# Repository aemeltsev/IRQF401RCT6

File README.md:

License
-------

IRQF401RCT6 schematic files and documentations are distributed under 
Creative Commons Attribution 4.0 International License.

Overview
--------
Simply dev. board based STM32F401RCT6. And includes in self: i2c eeprom memory and RS485 transceiver ic.

![PCB image][pcb_ray]

[pcb_ray]: https://github.com/aemeltsev/IRQF401RCT6/blob/master/doc/pcb_ray.png

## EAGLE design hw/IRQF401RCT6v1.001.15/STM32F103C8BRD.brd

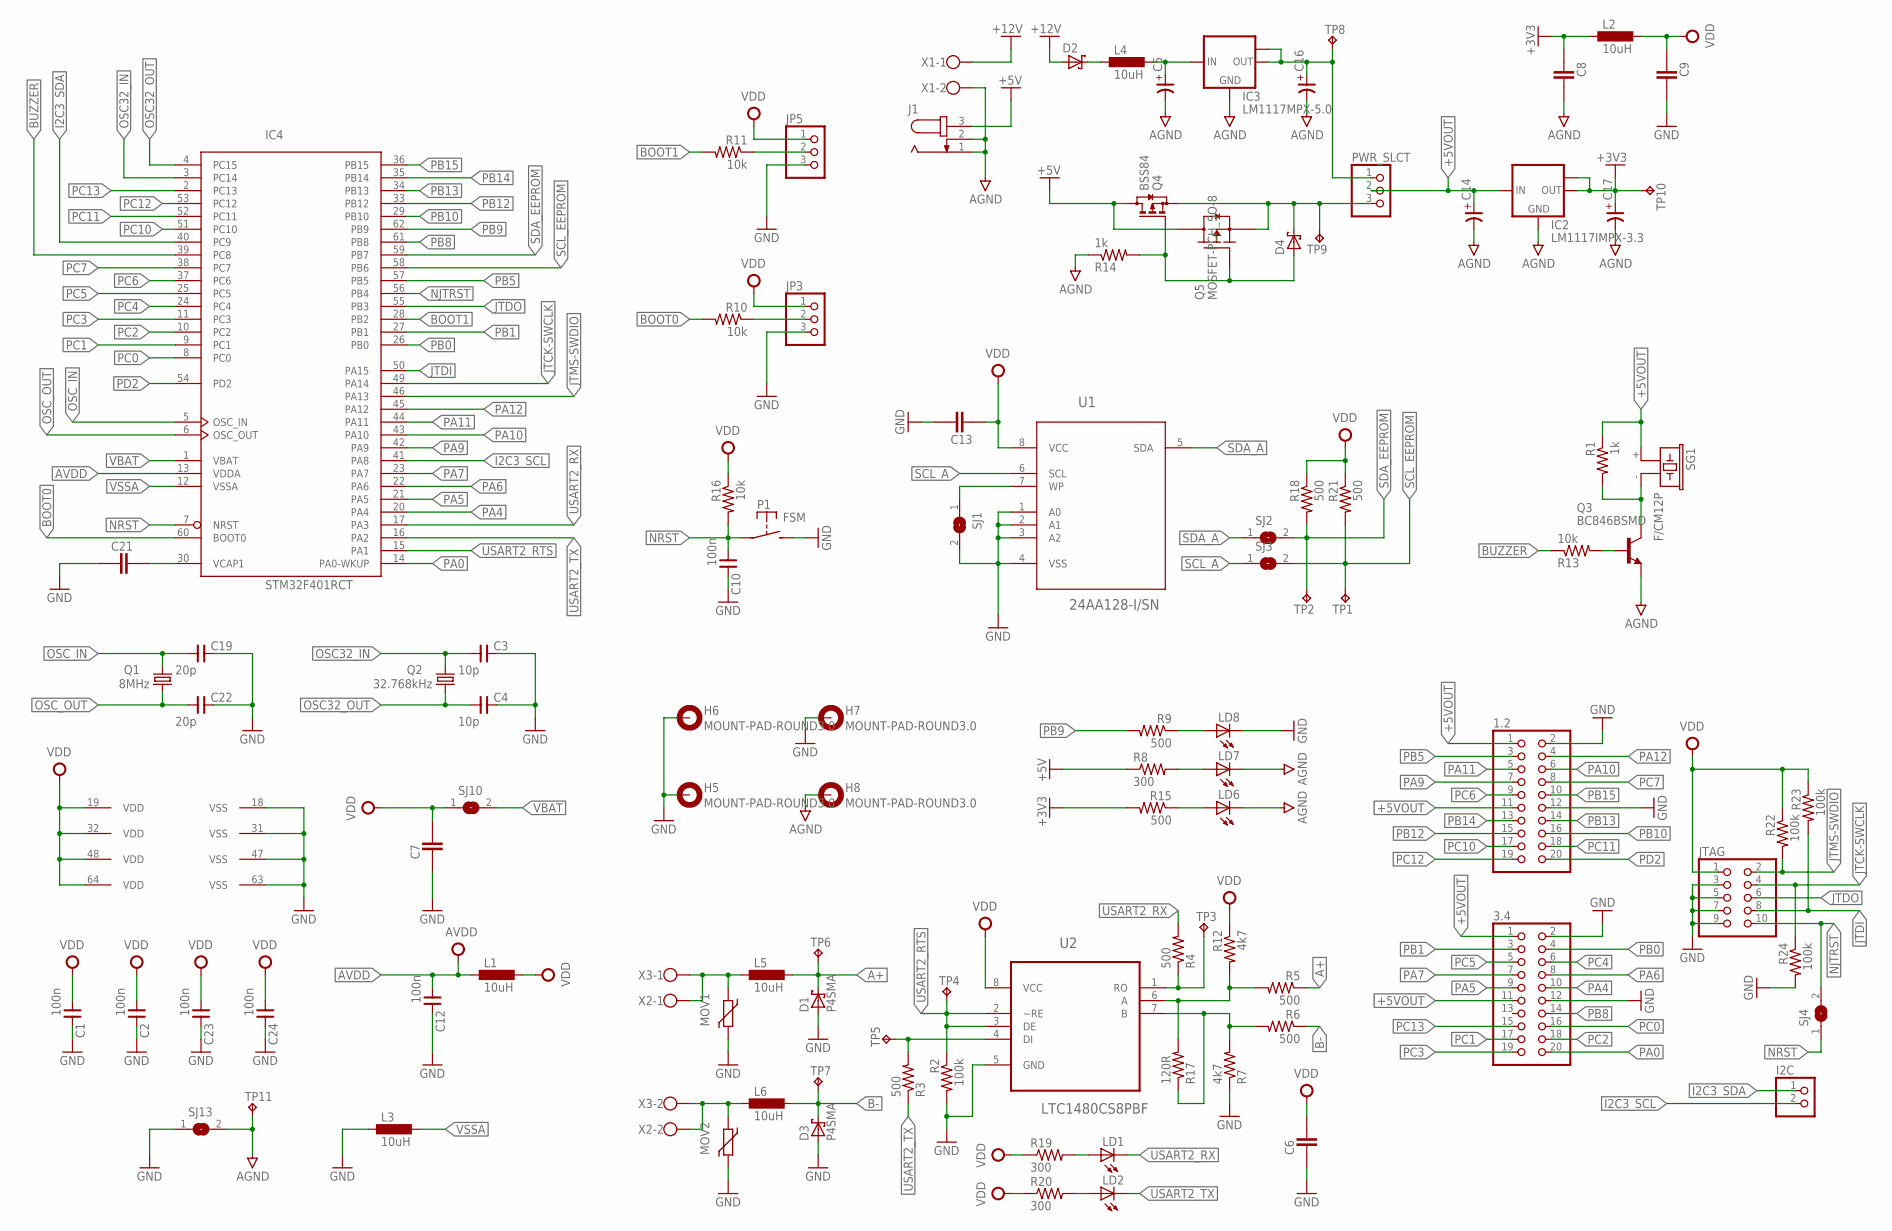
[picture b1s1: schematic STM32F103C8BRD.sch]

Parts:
1.2, 3.4: PINHD-2X10; 2X10
C1, C2, C10, C12, C23, C24: 100n; 0805
C3, C4: 10p; 0805
C5, C14: CP-3258-TE-B; 3528-TE-B
C6, C7, C8, C9, C13, C21: CAPACITOR_1206; CAPC3215X168N
C16, C17: CP-3216-TE-A; 3216-TE-A
C19, C22: 20p; 0805
D1, D3: P4SMA; SMB
D2, D4: SCHOTTKY_SMA; DIOM5326X292N
H5, H6, H7, H8: MOUNT-PAD-ROUND3.0; 3,0-PAD
I2C: PINHD-1X2; 1X02
IC2: LM1117IMPX-3.3; SOT223
IC3: LM1117MPX-5.0; SOT223
IC4: STM32F401RCT; LQFP64
J1: JACK-PLUG1; SPC4078
JP3, JP5: PINHD-1X3; 1X03
JTAG: PINHD-2X5; 2X05
L1, L2, L3, L4, L5, L6: 10uH; INDC1608X95N
LD1, LD2, LD6, LD7, LD8: LEDCHIPLED_0805; CHIPLED_0805
MOV1, MOV2: VARISTOR_0805; VARC2012X70N
P1: FSM
PWR_SLCT: PINHD-1X3; 1X03
Q1: 8MHz; HC49/S
Q2: 32.768kHz; TC26H
Q3: BC846BSMD; SOT23
Q4: BSS84; SOT23
Q5: MOSFET-PCH_SO-8; SOIC127P600X175-8AN
R1, R14: 1k; M0805
R2, R22, R23, R24: 100k; M0805
R3, R4, R5, R6, R9, R15, R18, R21: 500; M0805
R7, R12: 4k7; M0805
R8, R19, R20: 300; M0805
R10, R11, R13, R16: 10k; M0805
R17: 120R; M0805
SG1: F/CM12P
SJ1, SJ2, SJ3, SJ4, SJ10, SJ13: SJ
TP1, TP2, TP3, TP4, TP5, TP6, TP7, TP8, TP9, TP10, TP11: TPTP10R; TP10R
U1: 24AA128-I/SN; SOIC127P600X175-8N
U2: LTC1480CS8PBF; SOIC127P600X175-8N
X1, X2, X3: W237-102

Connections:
+3V3: C8.1, C17.+, IC2.2 (OUT), IC2.TAB (OUT1), L2.1, R15.2, TP10.TP
+5V: J1.3, Q4.3 (D), Q5.5 (D), R8.1
+5VOUT: 1.2.1, 1.2.11, 3.4.1, 3.4.11, C14.+, IC2.3 (IN), PWR_SLCT.2, R1.1, SG1.+ (1)
+12V: D2.A, X1.1
A+: D1.C, L5.2, R5.1, TP6.TP
AGND: C5.-, C8.2, C14.-, C16.-, C17.-, H8.B3,0, IC2.1 (GND), IC3.1 (GND), J1.1, J1.2, LD6.C, LD7.C, Q3.2 (E), R14.1, SJ13.2, TP11.TP, X1.2
AVDD: C12.1, IC4.13 (VDDA), L1.1
B-: D3.C, L6.2, R6.1, TP7.TP
BOOT0: IC4.60 (BOOT0), R10.2
BOOT1: IC4.28 (PB2), R11.2
BUZZER: IC4.39 (PC8), R13.1
GND: 1.2.2, 1.2.12, 3.4.2, 3.4.12, C1.2, C2.2, C3.2, C4.2, C6.1, C7.1, C9.2, C10.2, C12.2, C13.2, C19.2, C21.1, C22.2, C23.2, C24.2, D1.A, D3.A, H5.B3,0, H6.B3,0, H7.B3,0, IC4.18 (VSS), IC4.31 (VSS), IC4.47 (VSS), IC4.63 (VSS), JP3.3, JP5.3, JTAG.3, JTAG.5, JTAG.7, JTAG.9, L3.1, LD8.C, MOV1.1, MOV2.1, P1.P$2 (S), R2.2, R7.1, R24.2, SJ1.2, SJ13.1, U1.1 (A0), U1.2 (A1), U1.3 (A2), U1.4 (VSS), U2.5 (GND)
I2C3_SCL: I2C.2, IC4.41 (PA8)
I2C3_SDA: I2C.1, IC4.40 (PC9)
JTCK-SWCLK: IC4.49 (PA14), JTAG.4, R24.1
JTDI: IC4.50 (PA15), JTAG.8, R23.2
JTDO: IC4.55 (PB3), JTAG.6
JTMS-SWDIO: IC4.46 (PA13), JTAG.2, R22.2
unnamed: SJ1.1, U1.7 (WP)
unnamed: C21.2, IC4.30 (VCAP1)
unnamed: D2.K, L4.1
unnamed: R6.2, R7.2, R17.1, U2.7 (B)
unnamed: JP3.2, R10.1
unnamed: LD7.A, R8.2
unnamed: R3.2, TP5.TP, U2.4 (DI)
unnamed: R5.2, R12.2, R17.2, U2.6 (A)
unnamed: C5.+, IC3.3 (IN), L4.2
unnamed: L5.1, MOV1.2, X2.1, X3.1
unnamed: L6.1, MOV2.2, X2.2, X3.2
unnamed: R4.1, TP3.TP, U2.1 (RO)
unnamed: LD8.A, R9.1
unnamed: Q3.3 (C), R1.2, SG1.- (2)
unnamed: Q3.1 (B), R13.2
unnamed: LD6.A, R15.1
unnamed: LD1.A, R19.2
unnamed: LD2.A, R20.2
unnamed: D4.A, Q4.1 (G), Q5.4 (G), R14.2
unnamed: D4.K, PWR_SLCT.3, Q4.2 (S), Q5.1 (S), TP9.TP
NJTRST: IC4.56 (PB4), JTAG.10, SJ4.2
NRST: C10.1, IC4.7 (NRST), P1.P$1, R16.2, SJ4.1
OSC32_IN: C3.1, IC4.3 (PC14), Q2.2
OSC32_OUT: C4.1, IC4.4 (PC15), Q2.1
OSC_IN: C19.1, IC4.5 (OSC_IN), Q1.2
OSC_OUT: C22.1, IC4.6 (OSC_OUT), Q1.1
PA0: 3.4.20, IC4.14 (PA0-WKUP)
PA4: 3.4.10, IC4.20 (PA4)
PA5: 3.4.9, IC4.21 (PA5)
PA6: 3.4.8, IC4.22 (PA6)
PA7: 3.4.7, IC4.23 (PA7)
PA9: 1.2.7, IC4.42 (PA9)
PA10: 1.2.6, IC4.43 (PA10)
PA11: 1.2.5, IC4.44 (PA11)
PA12: 1.2.4, IC4.45 (PA12)
PB0: 3.4.4, IC4.26 (PB0)
PB1: 3.4.3, IC4.27 (PB1)
PB2: JP5.2, R11.1
PB5: 1.2.3, IC4.57 (PB5)
PB8: 3.4.14, IC4.61 (PB8)
PB9: IC4.62 (PB9), R9.2
PB10: 1.2.16, IC4.29 (PB10)
PB12: 1.2.15, IC4.33 (PB12)
PB13: 1.2.14, IC4.34 (PB13)
PB14: 1.2.13, IC4.35 (PB14)
PB15: 1.2.10, IC4.36 (PB15)
PC0: 3.4.16, IC4.8 (PC0)
PC1: 3.4.17, IC4.9 (PC1)
PC2: 3.4.18, IC4.10 (PC2)
PC3: 3.4.19, IC4.11 (PC3)
PC4: 3.4.6, IC4.24 (PC4)
PC5: 3.4.5, IC4.25 (PC5)
PC6: 1.2.9, IC4.37 (PC6)
PC7: 1.2.8, IC4.38 (PC7)
PC10: 1.2.17, IC4.51 (PC10)
PC11: 1.2.18, IC4.52 (PC11)
PC12: 1.2.19, IC4.53 (PC12)
PC13: 3.4.15, IC4.2 (PC13)
PD2: 1.2.20, IC4.54 (PD2)
SCL_A: SJ3.1, U1.6 (SCL)
SCL_EEPROM: IC4.58 (PB6), R21.2, SJ3.2, TP1.TP
SDA_A: SJ2.1, U1.5 (SDA)
SDA_EEPROM: IC4.59 (PB7), R18.2, SJ2.2, TP2.TP
USART2_RTS: IC4.15 (PA1), R2.1, TP4.TP, U2.2 (~RE), U2.3 (DE)
USART2_RX: IC4.17 (PA3), LD1.C, R4.2
USART2_TX: IC4.16 (PA2), LD2.C, R3.1
VBAT: IC4.1 (VBAT), SJ10.2
VCC_OUT: C16.+, IC3.2 (OUT), IC3.TAB (OUT1), PWR_SLCT.1, TP8.TP
VDD: C1.1, C2.1, C6.2, C7.2, C9.1, C13.1, C23.1, C24.1, IC4.19 (VDD), IC4.32 (VDD), IC4.48 (VDD), IC4.64 (VDD), JP3.1, JP5.1, JTAG.1, L1.2, L2.2, R12.1, R16.1, R18.1, R19.1, R20.1, R21.1, R22.1, R23.1, SJ10.1, U1.8 (VCC), U2.8 (VCC)
VSSA: IC4.12 (VSSA), L3.2

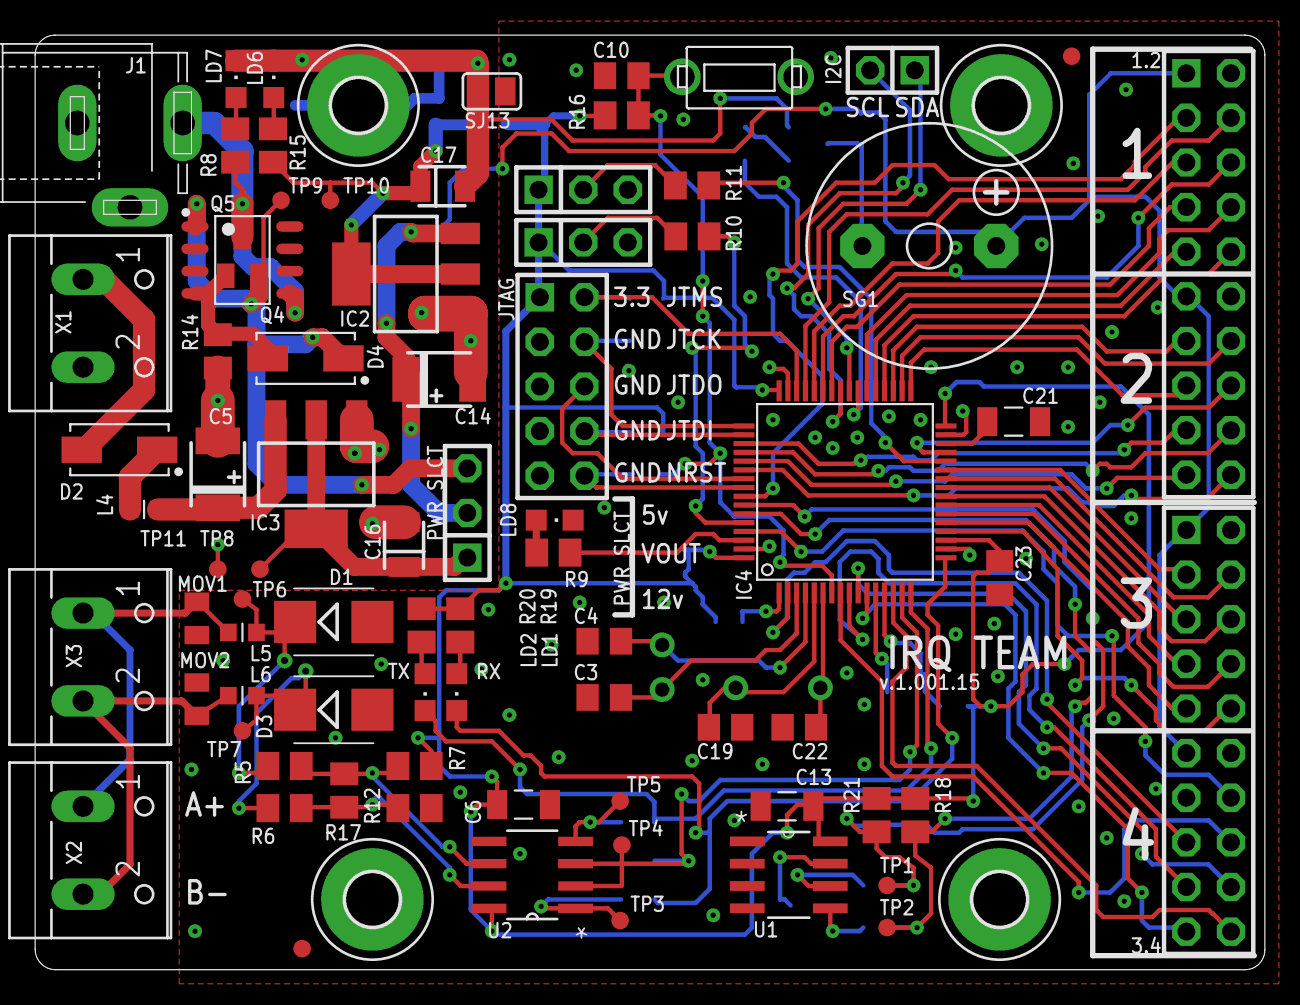
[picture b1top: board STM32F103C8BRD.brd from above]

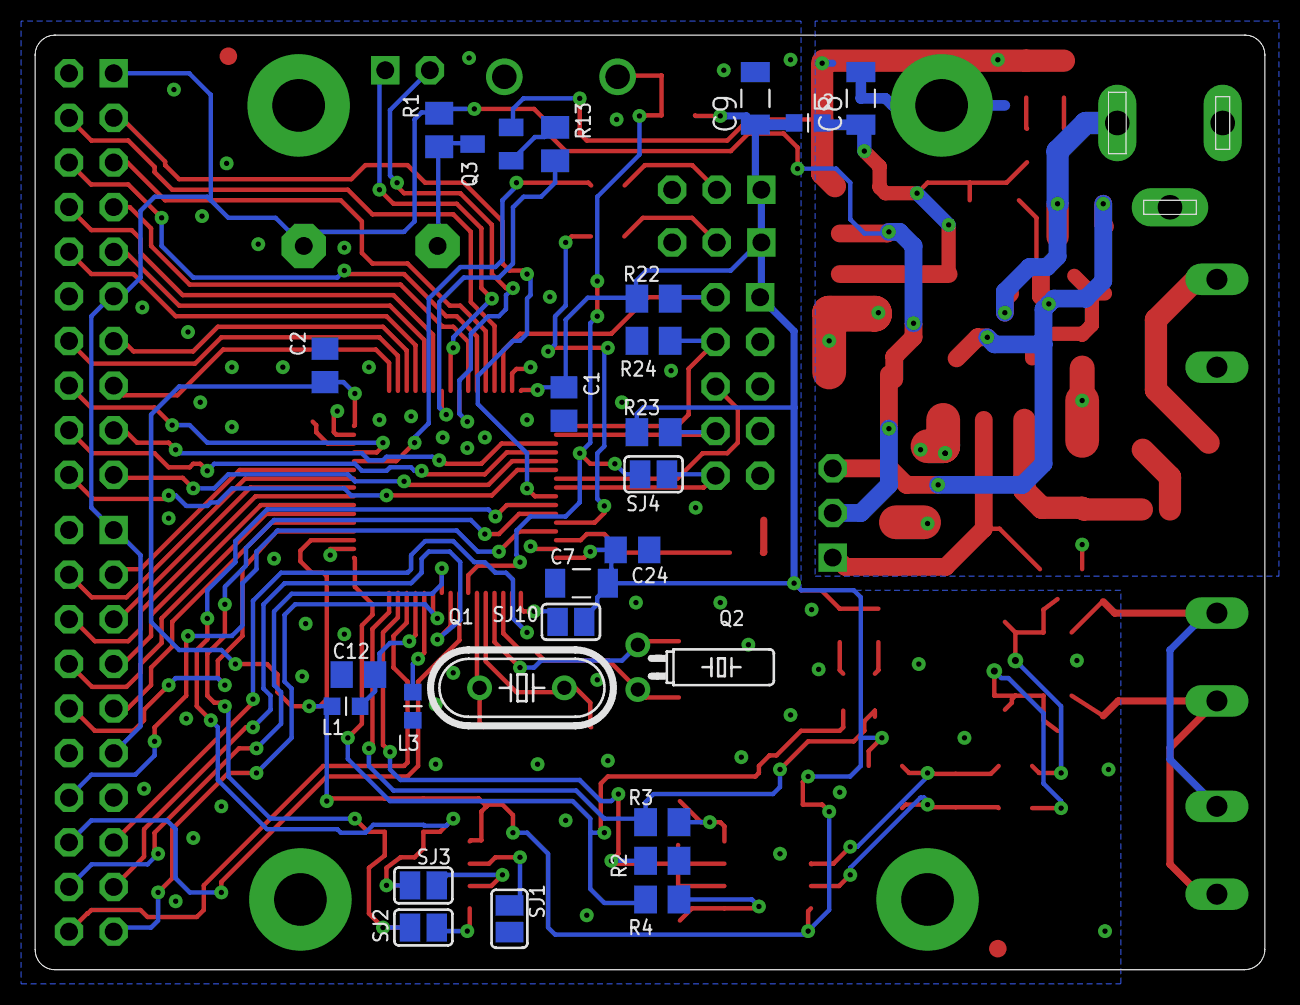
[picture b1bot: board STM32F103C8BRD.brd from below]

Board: 2 copper layers, 70.0 x 53.2 mm, 107 parts (26 on the bottom side), 88 nets.

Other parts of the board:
U$3, U$4: FIDUCIAL_G10

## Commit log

2017-10-18 :tada: Added .gitattributes & .gitignore files
2017-10-18 Add fifes
    Add schematic & doc files
2019-01-13 Create README.md
    add Readme
2019-01-13 Add files
    Add project files, data files and image. Include revise history.
2019-01-13 Rename
    Rename to IRQF401RCT6v1.002.revB.png
2019-01-13 Update README.md
    Add BRD image file
2019-01-13 Update README.md
    Update
2020-03-10 rev
    New revision
2024-01-12 Upgrage all
    Project update, using Kicad

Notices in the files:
parts and their libraries:
dicons: Copyright (C) 2004, Bob Starr (rtzaudio@mindspring.com)
supply0: Copyright (C) 2007, Bob Starr
